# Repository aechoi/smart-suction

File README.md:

# smart-suction

Single source of truth for the smart suction cup project — a suction cup end
effector that senses contact and alignment from capacitance changes across
eight electrodes.

```
smart-suction/
├── hardware/   KiCad sources for the sense boards and interconnect PCBs
├── firmware/   ESP32 end-effector firmware
├── software/   live capture, analysis, models
└── docs/       diagrams and notes
```

Each part has its own README with setup and usage.

## How the pieces fit

```mermaid
graph LR
    S[AD7746 CDC + 8 electrodes] -->|I2C| E[ESP32 + Ethernet PHY]
    E -->|UDP over PoE| H[Host PC: capcup.udp_receiver]
    H --> A[Analysis notebooks / models]
```

The end effector (`firmware/`) samples eight capacitance channels and streams
40-byte UDP packets to a host PC. `software/` records them and runs the
analysis and position-estimation models.

## How to record data

You will need:

- 1x PoE injector
- 2x ethernet cables
- 1x computer with `software/` installed

```mermaid
graph LR
    A[Outlet] -->|Power| B[PoE Injector]
    B <-->|LAN — ethernet| C[Host PC]
    B <-->|LAN + DC — ethernet| D[End Effector]
```

Then, from `software/`, run `python -m capcup.udp_receiver -f my_capture`.
Two windows open: a rolling time-domain plot and a radial plot.

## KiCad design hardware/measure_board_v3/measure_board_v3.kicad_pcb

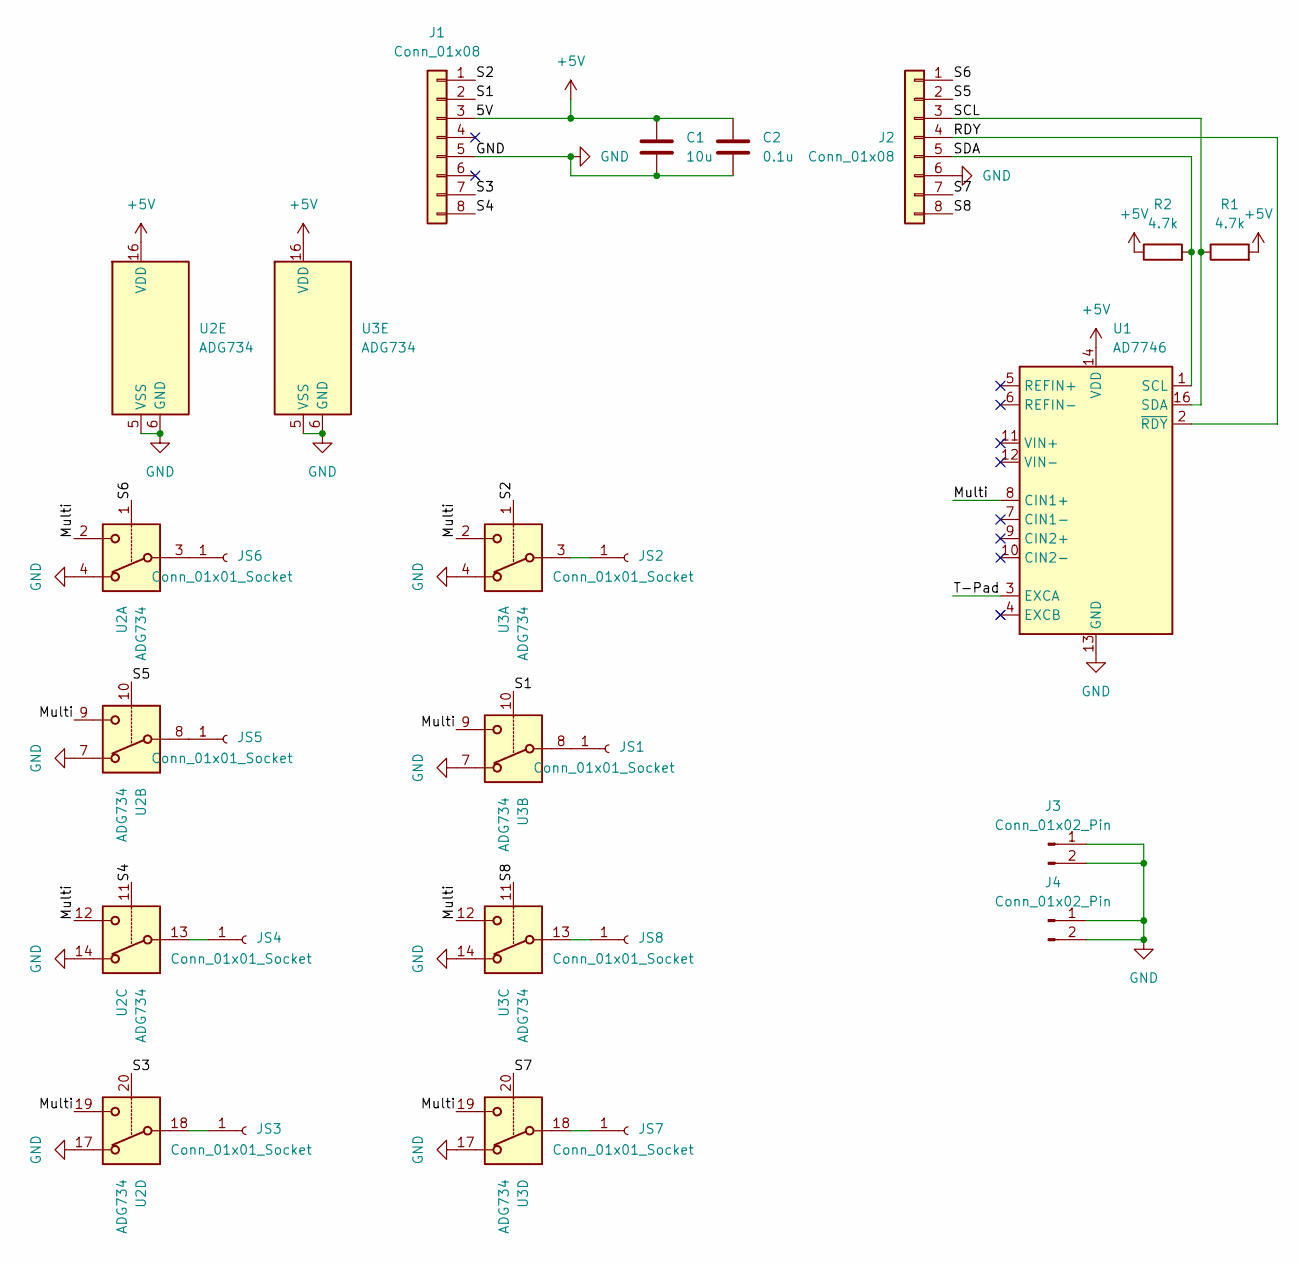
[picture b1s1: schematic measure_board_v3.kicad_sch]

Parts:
C1: 10u; C_1206_3216Metric_Pad1.33x1.80mm_HandSolder
C2: 0.1u; C_0603_1608Metric_Pad1.08x0.95mm_HandSolder
J1, J2: Conn_01x08; CON_525590870_MOL_8pv
J3, J4: Conn_01x02_Pin; CON_spring_00-9155-00X-85X-00X_KYOCERA
JS1, JS2, JS3, JS4, JS5, JS6, JS7, JS8: Conn_01x01_Socket; PinSocket_1x01_P2.54mm_Vertical
R1, R2: 4.7k; R_0603_1608Metric_Pad0.98x0.95mm_HandSolder
U1: AD7746; TSSOP-16_4.4x5mm_P0.65mm
U2, U3: ADG734; TSSOP-20_4.4x6.5mm_P0.65mm

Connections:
+5V: C1.1, C2.1, J1.3, R1.2, R2.1, U1.14 (VDD), U2.16 (VDD), U3.16 (VDD)
/Multi: U1.8 (CIN1+), U2.2, U2.9, U2.12, U2.19, U3.2, U3.9, U3.12, U3.19
/RDY: J2.4, U1.2 (~RDY)
/S1: J1.2, U3.10
/S2: J1.1, U3.1
/S3: J1.7, U2.20
/S4: J1.8, U2.11
/S5: J2.2, U2.10
/S6: J2.1, U2.1
/S7: J2.7, U3.20
/S8: J2.8, U3.11
/SCL: J2.3, R1.1, U1.16 (SDA)
/SDA: J2.5, R2.2, U1.1 (SCL)
/T-Pad: U1.3 (EXCA)
GND: C1.2, C2.2, J1.5, J2.6, J3.1, J3.2, J4.1, J4.2, U1.13 (GND), U2.4, U2.5 (VSS), U2.6 (GND), U2.7, U2.14, U2.17, U3.4, U3.5 (VSS), U3.6 (GND), U3.7, U3.14, U3.17
unnamed: JS1.1, U3.8
unnamed: JS2.1, U3.3
unnamed: JS3.1, U2.18
unnamed: JS4.1, U2.13
unnamed: JS5.1, U2.8
unnamed: JS6.1, U2.3
unnamed: JS7.1, U3.18
unnamed: JS8.1, U3.13

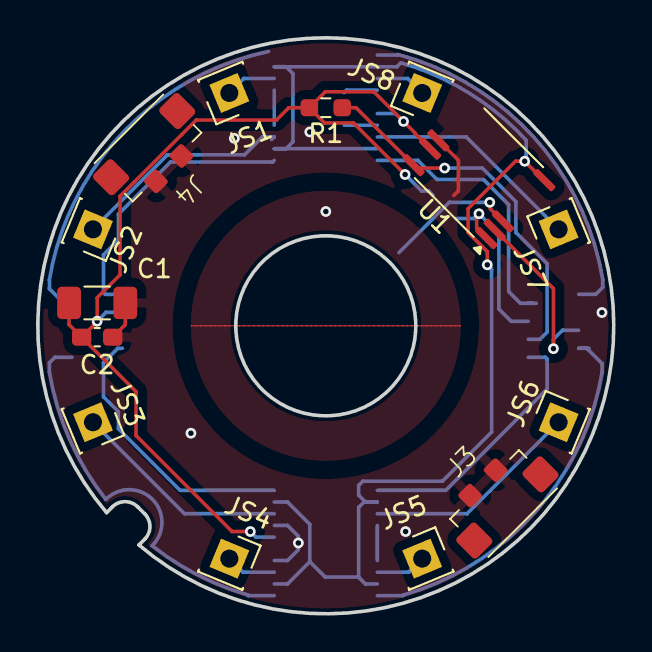
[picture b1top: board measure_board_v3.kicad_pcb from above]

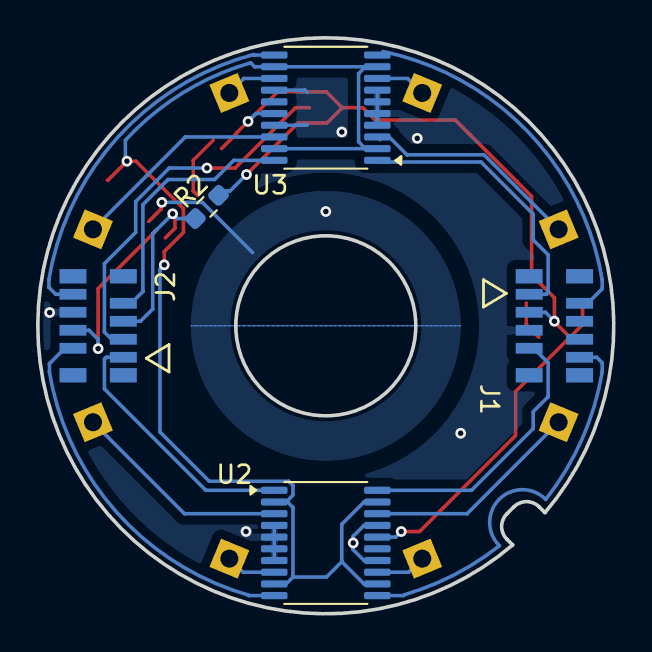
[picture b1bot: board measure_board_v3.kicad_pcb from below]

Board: 2 copper layers, 32.0 x 32.0 mm, 19 parts (5 on the bottom side), 22 nets.

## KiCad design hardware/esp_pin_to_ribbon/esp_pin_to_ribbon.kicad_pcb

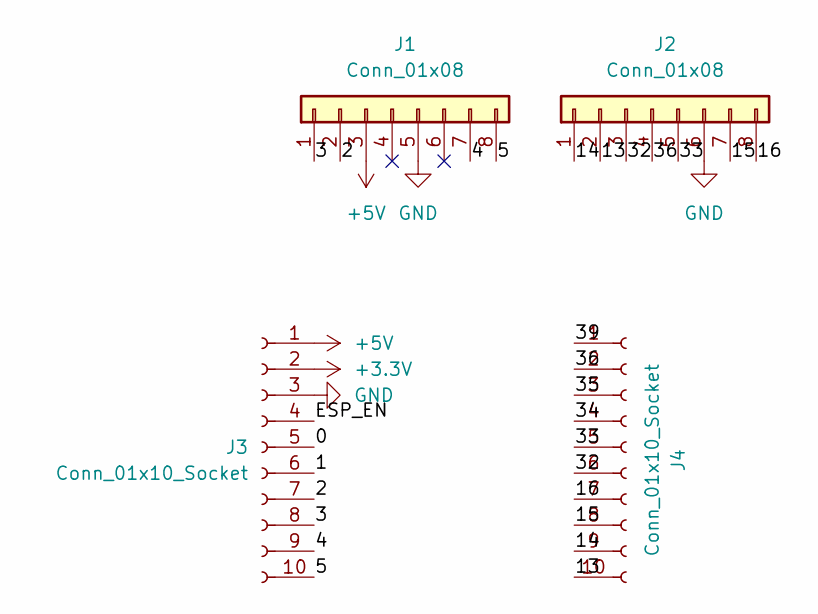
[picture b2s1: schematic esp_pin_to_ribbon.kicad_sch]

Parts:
J1, J2: Conn_01x08; CON_5051100892_MOL_8ph
J3, J4: Conn_01x10_Socket; PinSocket_1x10_P2.54mm_Vertical

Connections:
+3.3V: J3.2
+5V: J1.3, J3.1
/0: J3.5
/1: J3.6
/2: J1.2, J3.7
/3: J1.1, J3.8
/4: J1.7, J3.9
/5: J1.8, J3.10
/13: J2.2, J4.10
/14: J2.1, J4.9
/15: J2.7, J4.8
/16: J2.8, J4.7
/32: J2.3, J4.6
/33: J2.5, J4.5
/34: J4.4
/35: J4.3
/36: J2.4, J4.2
/39: J4.1
/ESP_EN: J3.4
GND: J1.5, J2.6, J3.3

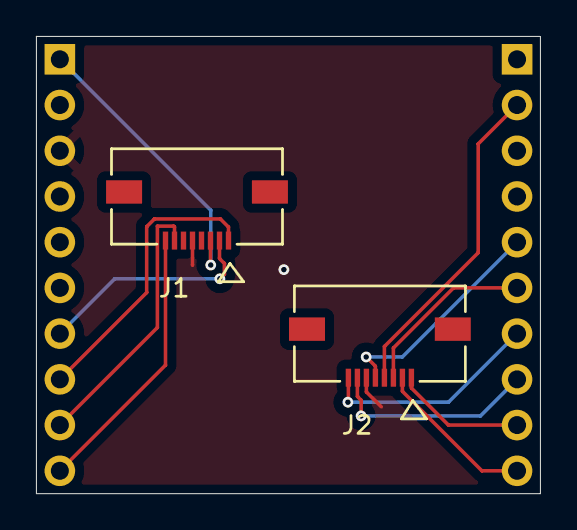
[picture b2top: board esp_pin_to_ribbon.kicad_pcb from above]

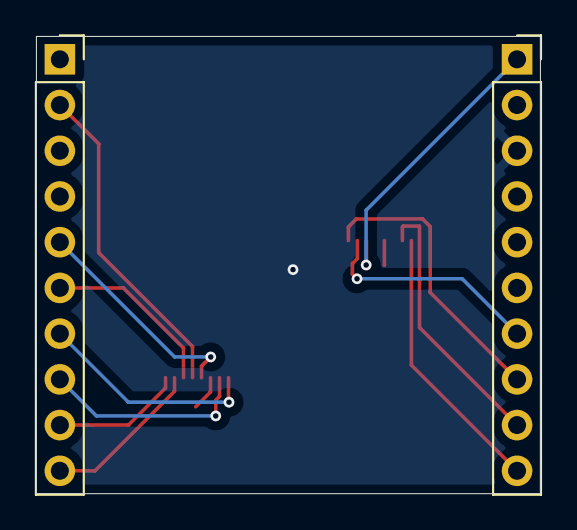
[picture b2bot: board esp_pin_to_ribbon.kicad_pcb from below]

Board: 2 copper layers, 28.0 x 25.4 mm, 4 parts (2 on the bottom side), 13 nets.

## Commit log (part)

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2025-02-22 initial commit with project set-up boiler plate
2025-02-22 add module for downloading datasets from googledrive
2025-02-22 rename project to capcup to remove hyphen. Also add tests for download_drive_data.py
2025-02-22 vestige from rename
2025-02-23 add eval_data_formatter.py which formats downloaded eval board test data into an EvalBoardData object
2025-02-26 add demo notebook showing analysis of initial capacitance data
2025-07-25 add recent tests
2025-09-08 add images for silver and printed tests
2025-09-30 add various tests and figures
2025-10-13 add ground truth generation files
2025-10-14 add 10x model and diagnostic plots)
2025-10-14 update record_serial to be more robust to buffer issues leading to dropped frames. Also increase baud
2025-10-15 add more plots for presentation
2025-10-15 add jubliee scripts
2025-10-15 clean up jubilee code
2025-10-15 add actuation signals to cycle
2025-10-15 add time limit to serial recording
2025-10-15 make visualizer optional
2025-10-15 debug rpi buffer buildup
2025-10-18 add geom viz, add lstm model
2025-10-18 add lstm model from desktop
2025-11-17 serial plotter low pass
2026-06-10 reorganizing the repo
2026-06-23 add board files
